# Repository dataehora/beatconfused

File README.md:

# BeatConfused

A small web studio of fast, elegant, install-free music tools. Every tool
is plain HTML, CSS and vanilla JavaScript with the Web Audio API — no build
step, no dependencies, no accounts, works offline after first load.

Live at [beatconfused.com](https://beatconfused.com).

## Tools

| Tool | Path | What it does |
| --- | --- | --- |
| **Metronome** | [`/metronome/`](https://beatconfused.com/metronome/) | Tap tempo, organized time signatures, beat subdivisions, counting modes, sound styles, and pulse / number / pendulum visuals. |
| **Tuner** | [`/tuner/`](https://beatconfused.com/tuner/) | Chromatic instrument tuner with needle, strobe and LED-meter displays, an adjustable A4 reference pitch, historical tuning standards, a test-tone generator, and a spectrum analyser. |
| **Octave Strobe Tuner** | [`/strobetuner/`](https://beatconfused.com/strobetuner/) | Identifies the note being played and shows its tuning across every octave at once on a single strobe disc. |
| **Chromatic Strobe Tuner** | [`/multistrobe/`](https://beatconfused.com/multistrobe/) | One dedicated strobe wheel per note, laid out like a piano keyboard, each with a ring per octave across the 88-key range. |
| **Luthier Tuning** | [`/luthier/`](https://beatconfused.com/luthier/) | Live spectrogram for luthiers and tuners: a slowly decaying live spectrum over a peak-hold record of every frequency, a sustain waterfall, harmonic guides, and a full-range / audible-only toggle. |

## Repository layout

```
index.html            Studio landing page (tool cards + JSON-LD)
styles.css             Landing-page styles
metronome/             Metronome — index.html, script.js, styles.css, Assets/
tuner/                 Tuner — index.html, script.js, styles.css
strobetuner/           Octave Strobe Tuner — index.html, script.js, styles.css
multistrobe/           Chromatic Strobe Tuner — index.html, script.js, styles.css
luthier/               Luthier Tuning (spectrogram) — index.html, script.js, styles.css
etutti/                eTutti (work in progress, unlisted) — Web MIDI page, Teensy firmware/,
                       hardware/ (eTuttino board v0.7 + case SPEC v9), manuais/, models/
binfacevsfarage/       Standalone browser game (not linked from the studio)
shared/                Assets shared across tools
CNAME, robots.txt, sitemap.xml   Hosting + crawl metadata
```

## Metronome controls

### Tempo
- **Slider** / **input field** — smooth or direct BPM entry (40–240)
- **+/- buttons** — step by 5 BPM
- **Tap tempo** — tap the button or press `T` to detect BPM
- **Arrow keys** — Up / Down to adjust BPM

### Beat settings
- **Time signature** — organized simple, compound and odd meters
- **Beat subdivision** — split each beat into more pulses
- **Tempo counting** — beat count, measure + beat, or hidden
- **Beat visual** — pulse, numbers, or pendulum
- **Sound style** — electronic, bossa, jazz, wood, cymbal, cowbell
- **Sound / vibration toggles** and **volume control**

### Keyboard shortcuts
- **Space** — start / stop
- **Arrow Up / Down** — BPM ±5
- **T** — tap tempo

### Custom sounds
Drop `{style}_{accent|beat|subdivision}` audio files (`.mp3`, then `.ogg`,
then `.wav`) into `metronome/Assets/` and they replace the synthesised click
for that combination. Anything not supplied keeps the built-in sound, so the
metronome always has audio even with no custom assets.

## Tuner controls

- **Start Tuner** — vintage-style slide switch above the display; turns the
  microphone on. A "no signal" sign appears below the display after ~3s of
  silence while running.
- **Display** — needle, strobe or LED meter
- **Input Monitor and Test Tone** — collapsed by default; microphone gain
  boost and a live level meter, plus a pure tone (with its own frequency,
  fine-tuning and volume controls) fed straight into the tuner and the
  speakers, no mic needed — the same panel /strobetuner/ and /multistrobe/
  use too
- **Spectrum Analyser** — vintage or modern style
- **Tuning Standard and Reference Pitch** — Equal Temperament plus
  Vallotti, Young II, 1/4-comma meantone and Just Intonation (each built
  from first principles), and an A4 reference from 392–466 Hz with
  historical presets (French Baroque, Baroque, Verdi, Standard, Modern,
  Italian Renaissance)
- **Frequency Table** — every note of an 88-key piano (octaves down the
  rows, notes across the columns) under the selected Tuning Standard and
  Reference Pitch, with a live cents deviation next to whichever note is
  sounding

## Luthier Tuning controls

- **Start Listening** — the same slide switch as the tuners (or `Space`)
- **Full range / Audible only** — everything the microphone captures (up
  to half its sample rate, with infrasound and ultrasound shaded) or just
  20 Hz – 20 kHz
- **Live curve** — the current spectrum; each frequency falls back at the
  **Decay speed** (dB/s) so a note's ring-out stays visible
- **Peak hold** — the pale-blue background graph: the loudest level each
  frequency has reached since the last **Reset peak hold**. **On** keeps
  it until reset; **Temporary** holds each maximum for 2 s, then lets it
  fall at the same Decay speed as the live curve; **Off** hides it
- **Sustain history** — a 12-second waterfall under the display
- **Cursor** — hover / tap for frequency, nearest note, live and peak dB,
  plus dashed guides at 2×, 3×, 4×… to judge inharmonicity
- **Input gain** — boosts quiet instruments

## Technical stack

- **HTML5 / CSS3** — semantic structure, gradients and animations
- **Web Audio API** — high-precision timing, autocorrelation pitch
  detection, Goertzel per-octave analysis for the strobe tools
- **Vanilla JavaScript** — no dependencies, no build step
- **Structured data + crawl files** — JSON-LD, `robots.txt`, `sitemap.xml`

## Development

Everything is static — serve the repo root with any static file server:

```bash
git clone https://github.com/dataehora/beatconfused.git
cd beatconfused
python3 -m http.server 8000
# then open http://localhost:8000/
```

## Deployment

Served via GitHub Pages on the `beatconfused.com` domain (`CNAME`). Any
static host with HTTPS works — no server-side code.

## License

MIT License — feel free to use and modify.

## Contributing

Contributions are welcome. Please open a Pull Request.

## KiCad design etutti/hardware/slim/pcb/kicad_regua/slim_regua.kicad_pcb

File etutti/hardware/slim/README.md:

# eTutti Slim

Versão de 32 teclas, a mais fina possível, independente do Student V4.

- `SPEC.md` — especificação vigente (R1SL). Comece por aqui.
- `conceito/` — material do conceito feito no Chat: renders, cortes, plantas, desenho dos knobs e scripts que geraram tudo.
- `fornecimento/gateron/` — desenho oficial e STEP do switch KS‑33D.
- Pastas que o Code vai criar: `pcb/` (KiCad), `case/`, `firmware/` e os relatórios `ELETRONICA.md`, `FIRMWARE.md`, `POSICIONAMENTO.md`, `ROTEAMENTO.md` e `FIT_CHECK.md`.

Etapas: 1) componentes e lógica → portão A · 2) posicionamento (régua e placa principal em sessões separadas) → portão B · 3) roteamento (idem) → portão C.

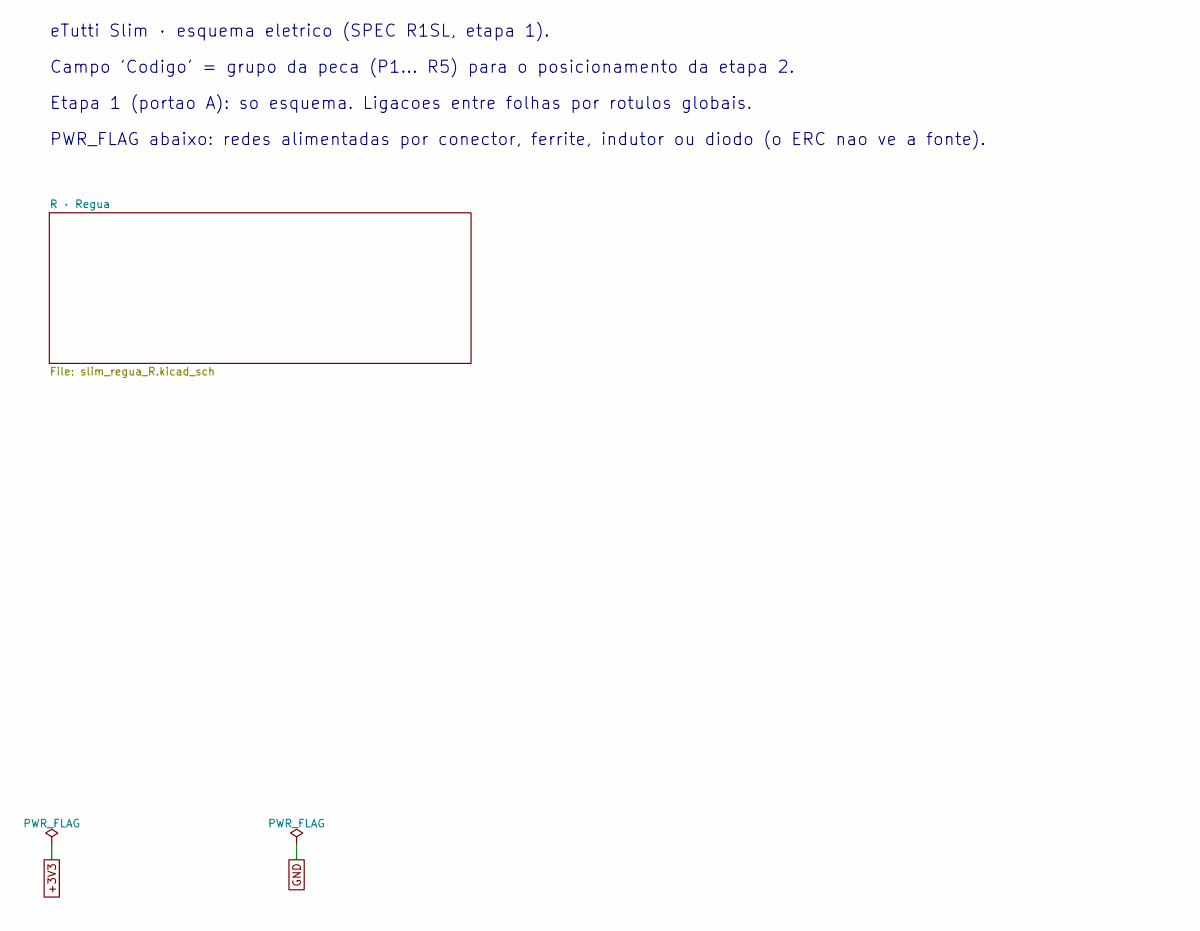
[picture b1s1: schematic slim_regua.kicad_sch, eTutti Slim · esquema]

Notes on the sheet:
eTutti Slim · esquema eletrico (SPEC R1SL, etapa 1).
Campo 'Codigo' = grupo da peca (P1... R5) para o posicionamento da etapa 2.
Etapa 1 (portao A): so esquema. Ligacoes entre folhas por rotulos globais.
PWR_FLAG abaixo: redes alimentadas por conector, ferrite, indutor ou diodo (o ERC nao ve a fonte).

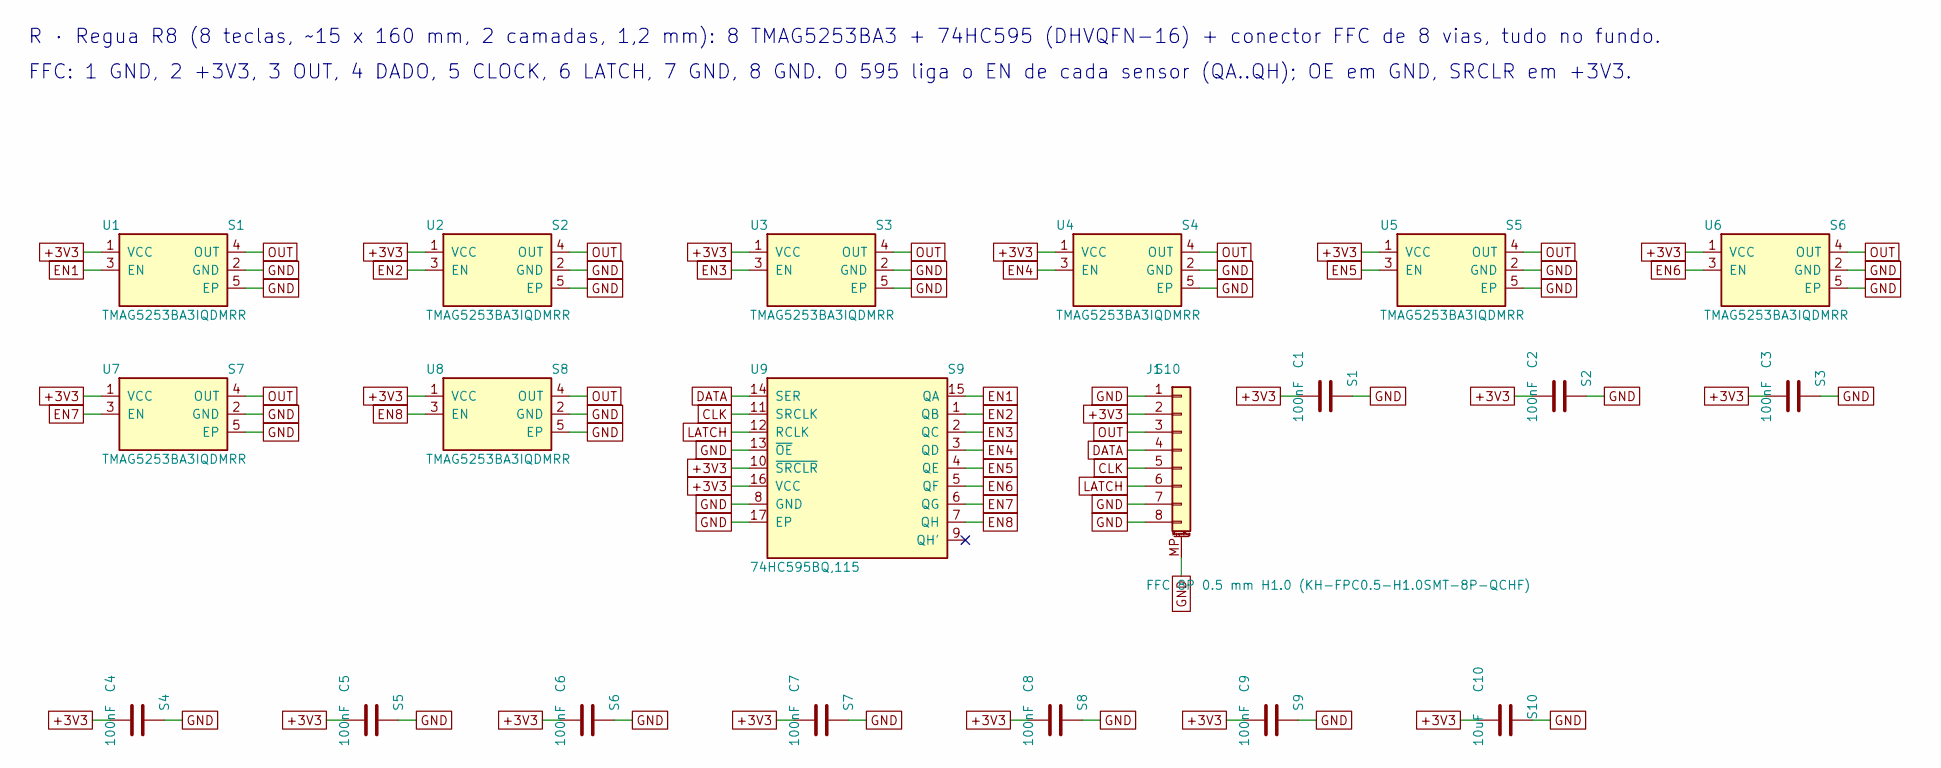
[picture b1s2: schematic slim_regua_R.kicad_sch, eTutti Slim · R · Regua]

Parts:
C1, C2, C3, C4, C5, C6, C7, C8, C9: 100nF; C_0402_1005Metric; LCSC C1525
C10: 10uF; C_0805_2012Metric; LCSC C15850
J1: FFC 8P 0.5 mm H1.0 (KH-FPC0.5-H1.0SMT-8P-QCHF); FFC_8P_0.5_KH-H1.0; LCSC C3250113
U1, U2, U3, U4, U5, U6, U7, U8: TMAG5253BA3IQDMRR; TMAG5253_X2SON4_EE; LCSC C22401868
U9: 74HC595BQ,115; HC595_DHVQFN16_EE; LCSC C730243

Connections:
+3V3: C1.1, C2.1, C3.1, C4.1, C5.1, C6.1, C7.1, C8.1, C9.1, C10.1, J1.2, U1.1 (VCC), U2.1 (VCC), U3.1 (VCC), U4.1 (VCC), U5.1 (VCC), U6.1 (VCC), U7.1 (VCC), U8.1 (VCC), U9.10 (~SRCLR), U9.16 (VCC)
CLK: J1.5, U9.11 (SRCLK)
DATA: J1.4, U9.14 (SER)
EN1: U1.3 (EN), U9.15 (QA)
EN2: U2.3 (EN), U9.1 (QB)
EN3: U3.3 (EN), U9.2 (QC)
EN4: U4.3 (EN), U9.3 (QD)
EN5: U5.3 (EN), U9.4 (QE)
EN6: U6.3 (EN), U9.5 (QF)
EN7: U7.3 (EN), U9.6 (QG)
EN8: U8.3 (EN), U9.7 (QH)
GND: C1.2, C2.2, C3.2, C4.2, C5.2, C6.2, C7.2, C8.2, C9.2, C10.2, J1.1, J1.7, J1.8, J1.MP (MountPin), U1.2 (GND), U1.5 (EP), U2.2 (GND), U2.5 (EP), U3.2 (GND), U3.5 (EP), U4.2 (GND), U4.5 (EP), U5.2 (GND), U5.5 (EP), U6.2 (GND), U6.5 (EP), U7.2 (GND), U7.5 (EP), U8.2 (GND), U8.5 (EP), U9.8 (GND), U9.13 (~OE), U9.17 (EP)
LATCH: J1.6, U9.12 (RCLK)
OUT: J1.3, U1.4 (OUT), U2.4 (OUT), U3.4 (OUT), U4.4 (OUT), U5.4 (OUT), U6.4 (OUT), U7.4 (OUT), U8.4 (OUT)

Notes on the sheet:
R · Regua R8 (8 teclas, ~15 x 160 mm, 2 camadas, 1,2 mm): 8 TMAG5253BA3 + 74HC595 (DHVQFN-16) + conector FFC de 8 vias, tudo no fundo.
FFC: 1 GND, 2 +3V3, 3 OUT, 4 DADO, 5 CLOCK, 6 LATCH, 7 GND, 8 GND. O 595 liga o EN de cada sensor (QA..QH); OE em GND, SRCLR em +3V3.

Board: 2 copper layers, 30 parts (20 on the bottom side), 14 nets, no tracks yet.

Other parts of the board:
H1, H2: MountingHole_2.2mm_M2
SW1, SW2, SW3, SW4, SW5, SW6, SW7, SW8: KS-33D (furos); KS33D_holes

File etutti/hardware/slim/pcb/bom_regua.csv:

lcsc,valor,classe_jlc,qtd,referencias,preco_unit_usd_est
C1525,100nF,Basic,9,C1 C2 C3 C4 C5 C6 C7 C8 C9,0.001
C15850,10uF,Basic,1,C10,0.008
C3250113,FFC 8P 0.5 mm H1.0 (KH-FPC0.5-H1.0SMT-8P-QCHF),Extended,1,J1,0.100
C22401868,TMAG5253BA3IQDMRR,Extended,8,U1 U2 U3 U4 U5 U6 U7 U8,0.600
C730243,"74HC595BQ,115",Extended,1,U9,0.176

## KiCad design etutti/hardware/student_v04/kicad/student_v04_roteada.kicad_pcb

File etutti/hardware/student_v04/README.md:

# eTutti Student V4 — base de trabalho

SPEC: `SPEC.md` (R1V4 + R2V4, do Chat; o Code nunca a edita). Relatórios do Code (português, citam "R2V4"):
`FIT_CHECK.md` (design), `ELETRONICA.md` (eletrônica), `FIRMWARE.md` (programação e som).

Esta pasta nasceu da `student_v03/` (R1V4, tarefa 1): só **scripts e fontes** (esquema, geometria, pcb, case, estudos,
fornecimento), sem `fab/`, renders, STEP/STL nem saídas geradas. A V3, a V2 e a V1 **não são alteradas**.
Fase B (R3V4): `pcb/schematic.py` (esquema V4, ERC), `pcb/posiciona_v4.py` (placa principal sem trilhas), `pcb/vistas_v4.py` (imagens), `bom_v4.py`; arquivos KiCad `kicad/student_v04.*`. Os demais scripts herdados da V3 (`build_sem_rota.py`, `pcb/build_board_v3.py`, `refaz_usb.py`...) não valem para a V4.
Páginas, Blender e passos de manual da V3 não foram copiados (página e manual ficam para depois, decisão 19).

## Ordem de execução (herdada da V3; ajustar à medida que a V4 diverge)

1. `python geometria.py` (stdlib).
2. `python pcb/schematic.py` (esquema + ERC + netlist), `pcb/export_furos.py` e `pcb/export_fp.py` (KiCad python).
3. Placa: `build_sem_rota.py` -> `pcb/build_board_v3.py` -> `pcb/troca_jack.py` -> `pcb/refaz_usb.py` -> `pcb/costura_usb.py` (KiCad python).
   Na V4 o posicionamento (Fase B) e o roteamento (Fase C, agente `roteamento`) são etapas separadas.
4. `fab.py`, `bom_v3.py`, `auditoria_pinos.py`.
5. Case (venv CadQuery): `case/case.py`, `case/fit_check.py`, `case/fit_extra.py`, `case/render.py`, `estudos/acustica.py`;
   `estudos/flexao.py` (KiCad python).

KiCad python: `C:/Program Files/KiCad/10.0/bin/python.exe`. CadQuery: `C:/Users/julia/.venvs/cadquery/Scripts/python.exe`.

## Réguas (R11V4)
Dois desenhos (R8 de 8 posições, R4 de 4), quatro variantes por BOM (R8, R8E, R4, R4E: "E" = com o OUT). Ordem, com `REGUA_N=8` ou `4`:
`python pcb/regua/schematic_regua.py` -> KiCad python `pcb/regua/posiciona_regua.py` -> KiCad python `pcb/regua/pacotes_regua.py` (BOM e CPL em `fab/regua/`) ->
KiCad python `MODO=regua PAINEL_N=2|4|5 pcb/regua/fab_regua.py` (painéis) -> venv CadQuery `pcb/regua/vistas_regua.py`; custo: `pcb/regua/custo_r11.py`.
Entrega ao roteamento: `pcb/regua/ROTEAMENTO_ENTREGA.md`; folha de cotação: `fab/regua/LEIAME_COTACAO.md`. Nunca rodar `posiciona_regua.py` sobre uma placa roteada (use `REGUA_BOARD`).

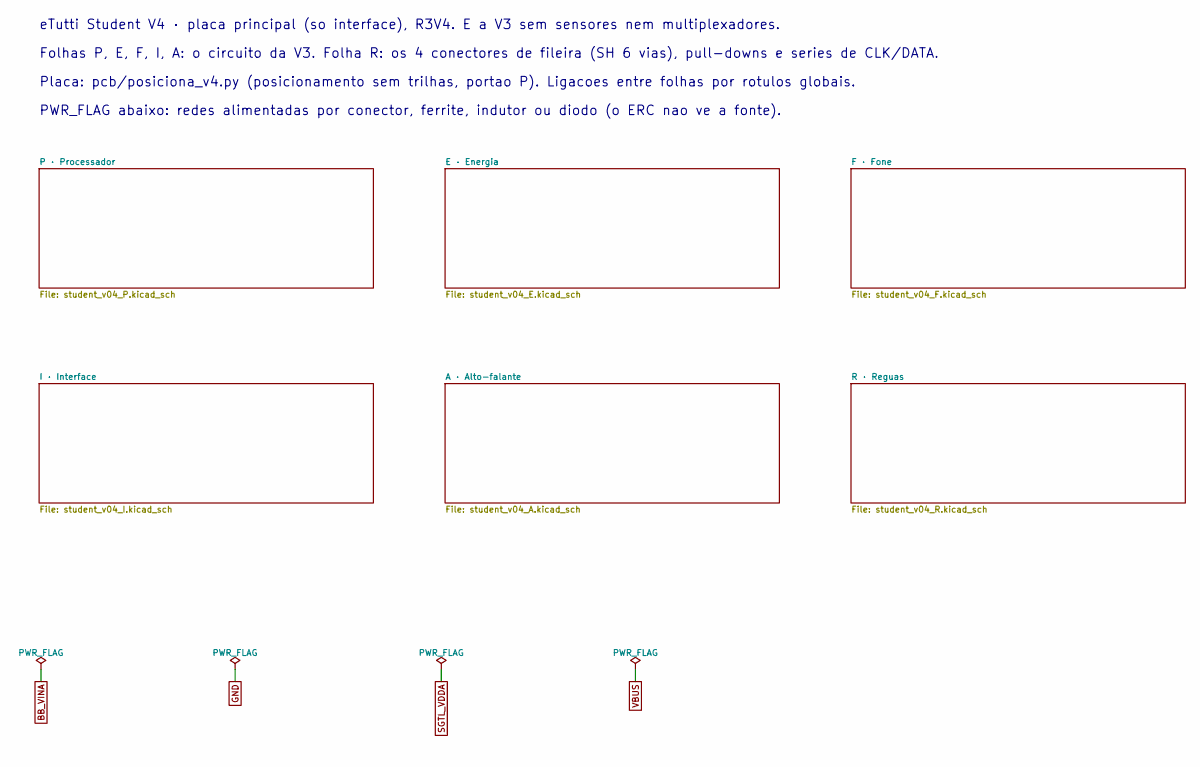
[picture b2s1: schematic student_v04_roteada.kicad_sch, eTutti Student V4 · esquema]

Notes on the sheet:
eTutti Student V4 · placa principal (so interface), R3V4. E a V3 sem sensores nem multiplexadores.
Folhas P, E, F, I, A: o circuito da V3. Folha R: os 4 conectores de fileira (SH 6 vias), pull-downs e series de CLK/DATA.
Placa: pcb/posiciona_v4.py (posicionamento sem trilhas, portao P). Ligacoes entre folhas por rotulos globais.
PWR_FLAG abaixo: redes alimentadas por conector, ferrite, indutor ou diodo (o ERC nao ve a fonte).

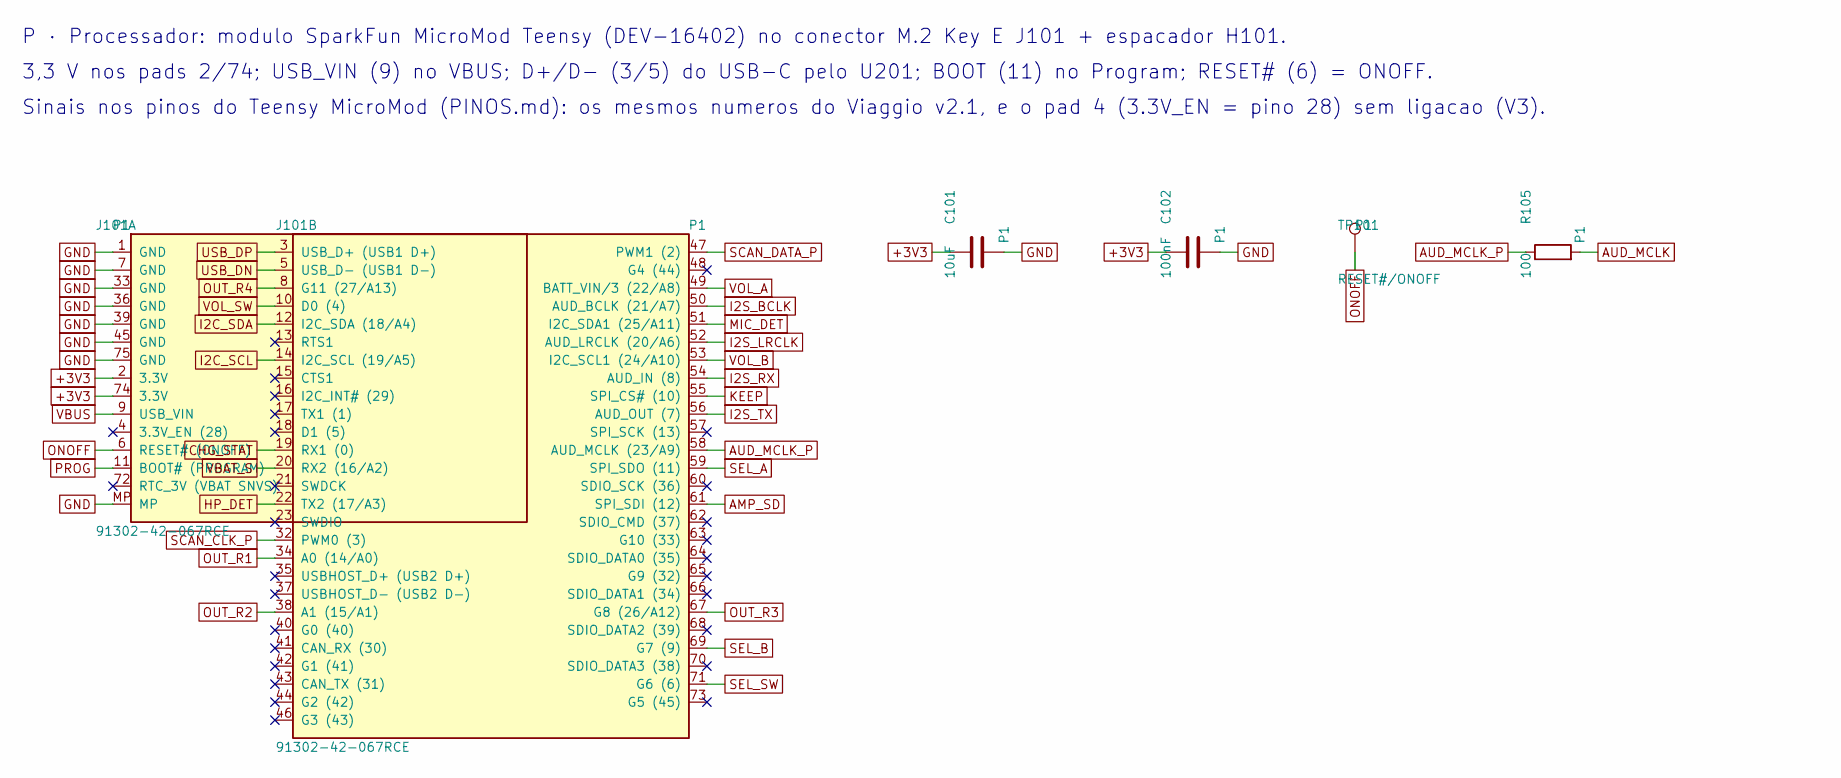
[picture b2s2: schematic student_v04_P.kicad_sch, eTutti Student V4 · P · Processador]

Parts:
C101: 10uF; C_0805_2012Metric; LCSC C15850
C102: 100nF; C_0402_1005Metric; LCSC C1525
J101: 91302-42-067RCE; M.2_E_H4.2_UMAX_91302-42-067; LCSC C48985906
R105: 100; R_0402_1005Metric; LCSC C25076
TP101: RESET#/ONOFF; TestPoint_Pad_D1.5mm

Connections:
+3V3: C101.1, C102.1, J101.2 (3.3V), J101.74 (3.3V); also elsewhere on the board
AMP_SD: J101.61 (SPI_SDI (12)); also elsewhere on the board
AUD_MCLK: R105.2; also elsewhere on the board
AUD_MCLK_P: J101.58 (AUD_MCLK (23/A9)), R105.1
CHG_STAT: J101.19 (RX1 (0)); also elsewhere on the board
GND: C101.2, C102.2, J101.1 (GND), J101.7 (GND), J101.33 (GND), J101.36 (GND), J101.39 (GND), J101.45 (GND), J101.75 (GND), J101.MP; also elsewhere on the board
HP_DET: J101.22 (TX2 (17/A3)); also elsewhere on the board
I2C_SCL: J101.14 (I2C_SCL (19/A5)); also elsewhere on the board
I2C_SDA: J101.12 (I2C_SDA (18/A4)); also elsewhere on the board
I2S_BCLK: J101.50 (AUD_BCLK (21/A7)); also elsewhere on the board
I2S_LRCLK: J101.52 (AUD_LRCLK (20/A6)); also elsewhere on the board
I2S_RX: J101.54 (AUD_IN (8)); also elsewhere on the board
I2S_TX: J101.56 (AUD_OUT (7)); also elsewhere on the board
KEEP: J101.55 (SPI_CS# (10)); also elsewhere on the board
MIC_DET: J101.51 (I2C_SDA1 (25/A11)); also elsewhere on the board
ONOFF: J101.6 (RESET# (ONOFF)), TP101.1; also elsewhere on the board
OUT_R1: J101.34 (A0 (14/A0)); also elsewhere on the board
OUT_R2: J101.38 (A1 (15/A1)); also elsewhere on the board
OUT_R3: J101.67 (G8 (26/A12)); also elsewhere on the board
OUT_R4: J101.8 (G11 (27/A13)); also elsewhere on the board
PROG: J101.11 (BOOT# (PROGRAM)); also elsewhere on the board
SCAN_CLK_P: J101.32 (PWM0 (3)); also elsewhere on the board
SCAN_DATA_P: J101.47 (PWM1 (2)); also elsewhere on the board
SEL_A: J101.59 (SPI_SDO (11)); also elsewhere on the board
SEL_B: J101.69 (G7 (9)); also elsewhere on the board
SEL_SW: J101.71 (G6 (6)); also elsewhere on the board
USB_DN: J101.5 (USB_D- (USB1 D-)); also elsewhere on the board
USB_DP: J101.3 (USB_D+ (USB1 D+)); also elsewhere on the board
VBAT_S: J101.20 (RX2 (16/A2)); also elsewhere on the board
VBUS: J101.9 (USB_VIN); also elsewhere on the board
VOL_A: J101.49 (BATT_VIN/3 (22/A8)); also elsewhere on the board
VOL_B: J101.53 (I2C_SCL1 (24/A10)); also elsewhere on the board
VOL_SW: J101.10 (D0 (4)); also elsewhere on the board

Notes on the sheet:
P · Processador: modulo SparkFun MicroMod Teensy (DEV-16402) no conector M.2 Key E J101 + espacador H101.
3,3 V nos pads 2/74; USB_VIN (9) no VBUS; D+/D- (3/5) do USB-C pelo U201; BOOT (11) no Program; RESET# (6) = ONOFF.
Sinais nos pinos do Teensy MicroMod (PINOS.md): os mesmos numeros do Viaggio v2.1, e o pad 4 (3.3V_EN = pino 28) sem ligacao (V3).

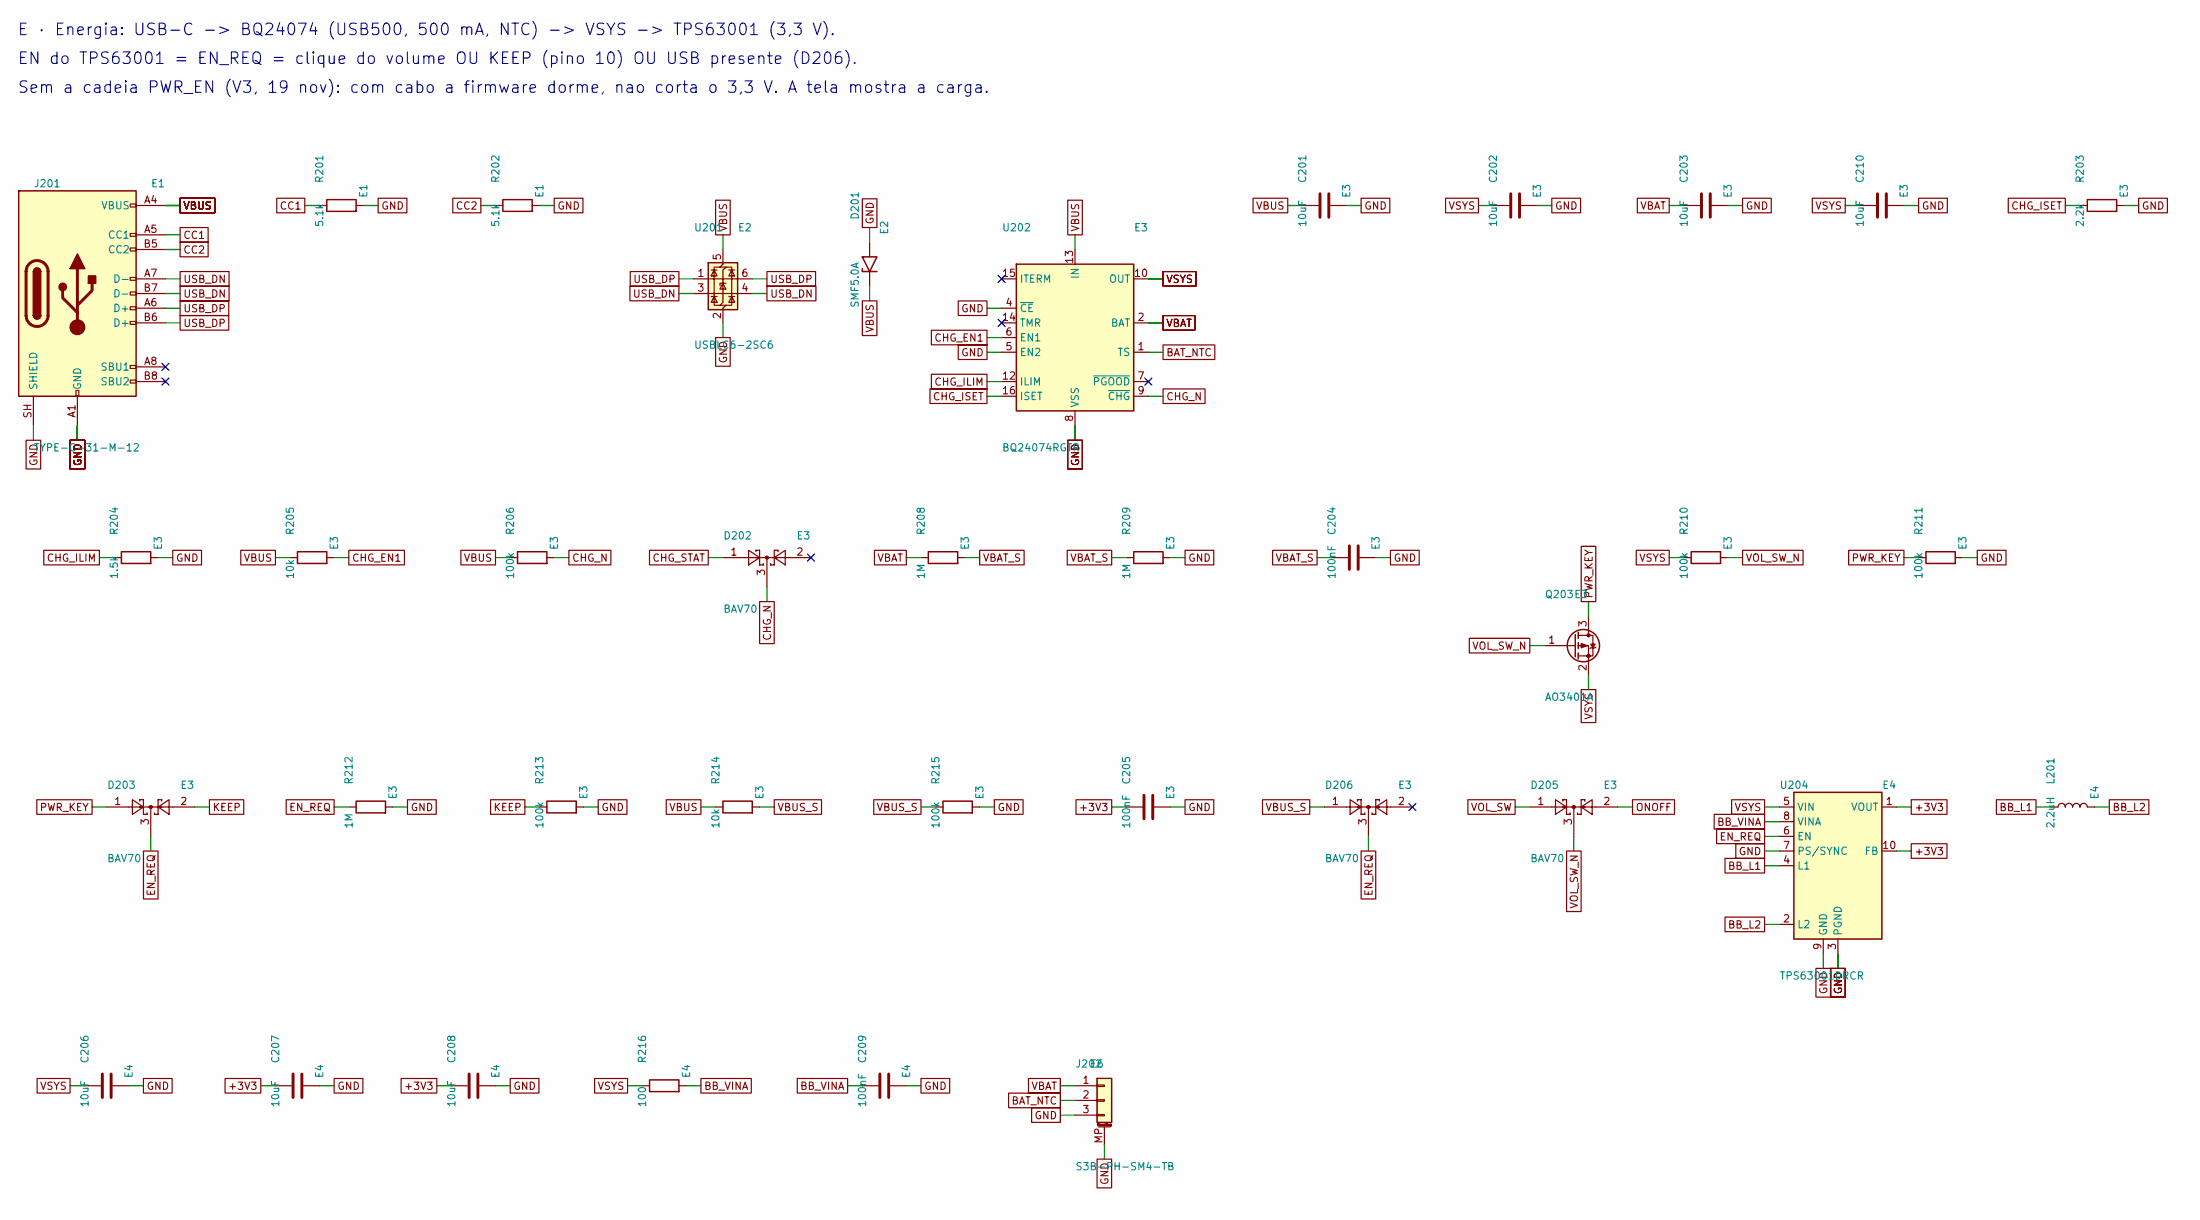
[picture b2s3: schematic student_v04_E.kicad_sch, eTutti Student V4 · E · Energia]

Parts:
C201, C202, C203, C206, C207, C208: 10uF; C_0805_2012Metric; LCSC C15850
C204, C205, C209: 100nF; C_0402_1005Metric; LCSC C1525
C210: 10uF; C_0603_1608Metric; LCSC C19702
D201: SMF5.0A; D_SOD-123F; LCSC C151296
D202, D203, D205, D206: BAV70; SOT-23; LCSC C68978
J201: TYPE-C-31-M-12; USB_C_Receptacle_HRO_TYPE-C-31-M-12; LCSC C165948
J202: S3B-PH-SM4-TB; JST_PH_S3B-PH-SM4-TB_1x03-1MP_P2.00mm_Horizontal; LCSC C265101
L201: 2.2uH; L_Changjiang_FNR4020S; LCSC C167825
Q203: AO3401A; SOT-23; LCSC C15127
R201, R202: 5.1k; R_0402_1005Metric; LCSC C25905
R203: 2.2k; R_0402_1005Metric; LCSC C25879
R204: 1.5k; R_0402_1005Metric; LCSC C25867
R205, R214: 10k; R_0402_1005Metric; LCSC C25744
R206, R210, R211, R213, R215: 100k; R_0402_1005Metric; LCSC C25741
R208, R209, R212: 1M; R_0402_1005Metric; LCSC C26083
R216: 100; R_0402_1005Metric; LCSC C25076
U201: USBLC6-2SC6; SOT-23-6; LCSC C7519
U202: BQ24074RGTR; VQFN-16-1EP_3x3mm_P0.5mm_EP1.6x1.6mm; LCSC C54313
U204: TPS63001DRCR; Texas_DRC0010J; LCSC C28060

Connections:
+3V3: C205.1, C207.1, C208.1, U204.1 (VOUT), U204.10 (FB); also elsewhere on the board
BAT_NTC: J202.2, U202.1 (TS)
BB_L1: L201.1, U204.4 (L1)
BB_L2: L201.2, U204.2 (L2)
BB_VINA: C209.1, R216.2, U204.8 (VINA)
CC1: J201.A5 (CC1), R201.1
CC2: J201.B5 (CC2), R202.1
CHG_EN1: R205.2, U202.6 (EN1)
CHG_ILIM: R204.1, U202.12 (ILIM)
CHG_ISET: R203.1, U202.16 (ISET)
CHG_N: D202.3, R206.2, U202.9 (~CHG)
CHG_STAT: D202.1; also elsewhere on the board
EN_REQ: D203.3, D206.3, R212.1, U204.6 (EN)
GND: C201.2, C202.2, C203.2, C204.2, C205.2, C206.2, C207.2, C208.2, C209.2, C210.2, D201.2 (A2), J201.A1 (GND), J201.A12 (GND), J201.B1 (GND), J201.B12 (GND), J201.SH (SHIELD), J202.3, J202.MP (MountPin), R201.2, R202.2, R203.2, R204.2, R209.2, R211.2, R212.2, R213.2, R215.2, U201.2 (GND), U202.4 (~CE), U202.5 (EN2), U202.8 (VSS), U202.17 (VSS), U204.3 (PGND), U204.7 (PS/SYNC), U204.9 (GND), U204.11 (PGND); also elsewhere on the board
KEEP: D203.2, R213.1; also elsewhere on the board
ONOFF: D205.2; also elsewhere on the board
PWR_KEY: D203.1, Q203.3 (D), R211.1
USB_DN: J201.A7 (D-), J201.B7 (D-), U201.3 (I/O2), U201.4 (I/O2); also elsewhere on the board
USB_DP: J201.A6 (D+), J201.B6 (D+), U201.1 (I/O1), U201.6 (I/O1); also elsewhere on the board
VBAT: C203.1, J202.1, R208.1, U202.2 (BAT), U202.3 (BAT)
VBAT_S: C204.1, R208.2, R209.1; also elsewhere on the board
VBUS: C201.1, D201.1 (A1), J201.A4 (VBUS), J201.A9 (VBUS), J201.B4 (VBUS), J201.B9 (VBUS), R205.1, R206.1, R214.1, U201.5 (VBUS), U202.13 (IN); also elsewhere on the board
VBUS_S: D206.1, R214.2, R215.1
VOL_SW: D205.1; also elsewhere on the board
VOL_SW_N: D205.3, Q203.1 (G), R210.2; also elsewhere on the board
VSYS: C202.1, C206.1, C210.1, Q203.2 (S), R210.1, R216.1, U202.10 (OUT), U202.11 (OUT), U204.5 (VIN); also elsewhere on the board

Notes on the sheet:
E · Energia: USB-C -> BQ24074 (USB500, 500 mA, NTC) -> VSYS -> TPS63001 (3,3 V).
EN do TPS63001 = EN_REQ = clique do volume OU KEEP (pino 10) OU USB presente (D206).
Sem a cadeia PWR_EN (V3, 19 nov): com cabo a firmware dorme, nao corta o 3,3 V. A tela mostra a carga.

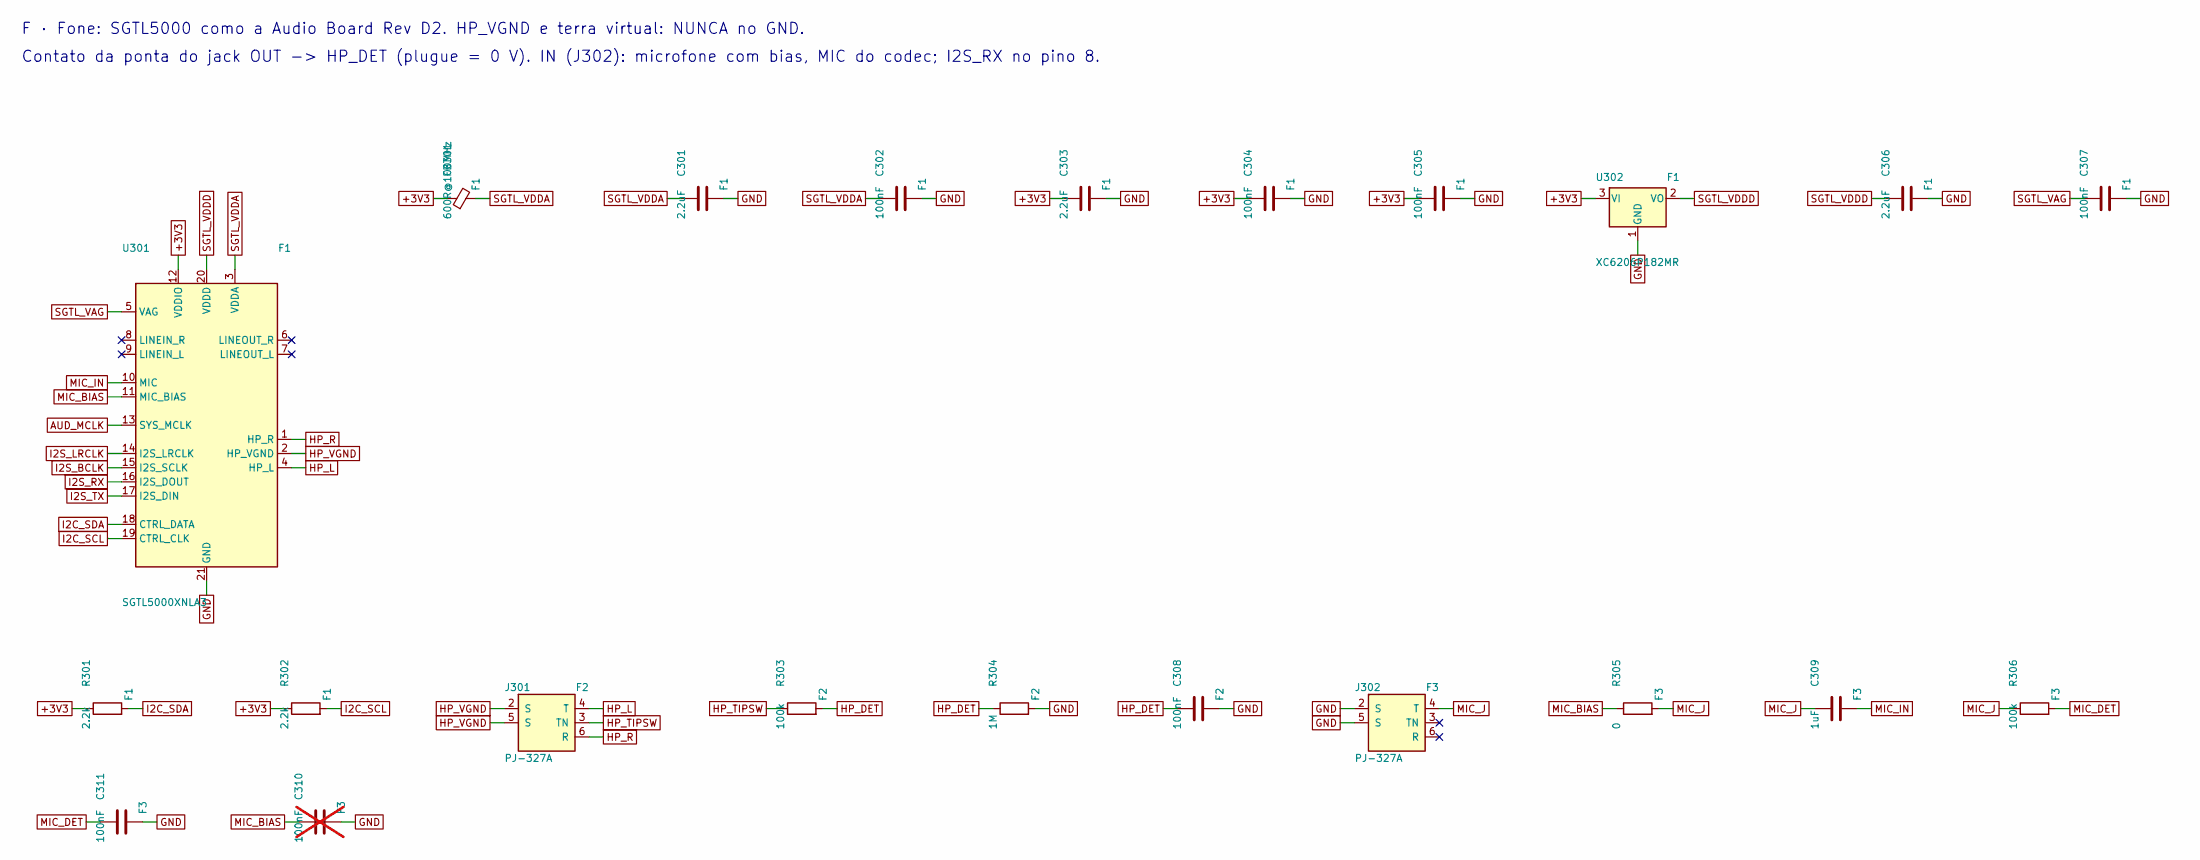
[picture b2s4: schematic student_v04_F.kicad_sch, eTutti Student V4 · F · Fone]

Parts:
C301, C303, C306: 2.2uF; C_0402_1005Metric; LCSC C12530
C302, C304, C305, C307, C308, C311: 100nF; C_0402_1005Metric; LCSC C1525
C309: 1uF; C_0402_1005Metric; LCSC C52923
C310: 100nF; C_0402_1005Metric; LCSC C1525; not fitted
FB301: 600R@100MHz; L_0603_1608Metric; LCSC C1002
J301, J302: PJ-327A; Jack_3.5mm_PJ-327A_SMD; LCSC C49284723
R301, R302: 2.2k; R_0402_1005Metric; LCSC C25879
R303, R306: 100k; R_0402_1005Metric; LCSC C25741
R304: 1M; R_0402_1005Metric; LCSC C26083
R305: 0; R_0402_1005Metric; LCSC C17168
U301: SGTL5000XNLA3; QFN-20-1EP_3x3mm_P0.4mm_EP1.65x1.65mm; LCSC C2651833
U302: XC6206P182MR; SOT-23-3; LCSC C347373

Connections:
+3V3: C303.1, C304.1, C305.1, FB301.1, R301.1, R302.1, U301.12 (VDDIO), U302.3 (VI); also elsewhere on the board
AUD_MCLK: U301.13 (SYS_MCLK); also elsewhere on the board
GND: C301.2, C302.2, C303.2, C304.2, C305.2, C306.2, C307.2, C308.2, C310.2, C311.2, J302.2 (S), J302.5 (S), R304.2, U301.21 (GND), U302.1 (GND); also elsewhere on the board
HP_DET: C308.1, R303.2, R304.1; also elsewhere on the board
HP_L: J301.4 (T), U301.4 (HP_L)
HP_R: J301.6 (R), U301.1 (HP_R)
HP_TIPSW: J301.3 (TN), R303.1
HP_VGND: J301.2 (S), J301.5 (S), U301.2 (HP_VGND)
I2C_SCL: R302.2, U301.19 (CTRL_CLK); also elsewhere on the board
I2C_SDA: R301.2, U301.18 (CTRL_DATA); also elsewhere on the board
I2S_BCLK: U301.15 (I2S_SCLK); also elsewhere on the board
I2S_LRCLK: U301.14 (I2S_LRCLK); also elsewhere on the board
I2S_RX: U301.16 (I2S_DOUT); also elsewhere on the board
I2S_TX: U301.17 (I2S_DIN); also elsewhere on the board
MIC_BIAS: C310.1, R305.1, U301.11 (MIC_BIAS)
MIC_DET: C311.1, R306.2; also elsewhere on the board
MIC_IN: C309.2, U301.10 (MIC)
MIC_J: C309.1, J302.4 (T), R305.2, R306.1
SGTL_VAG: C307.1, U301.5 (VAG)
SGTL_VDDA: C301.1, C302.1, FB301.2, U301.3 (VDDA)
SGTL_VDDD: C306.1, U301.20 (VDDD), U302.2 (VO)

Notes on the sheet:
F · Fone: SGTL5000 como a Audio Board Rev D2. HP_VGND e terra virtual: NUNCA no GND.
Contato da ponta do jack OUT -> HP_DET (plugue = 0 V). IN (J302): microfone com bias, MIC do codec; I2S_RX no pino 8.

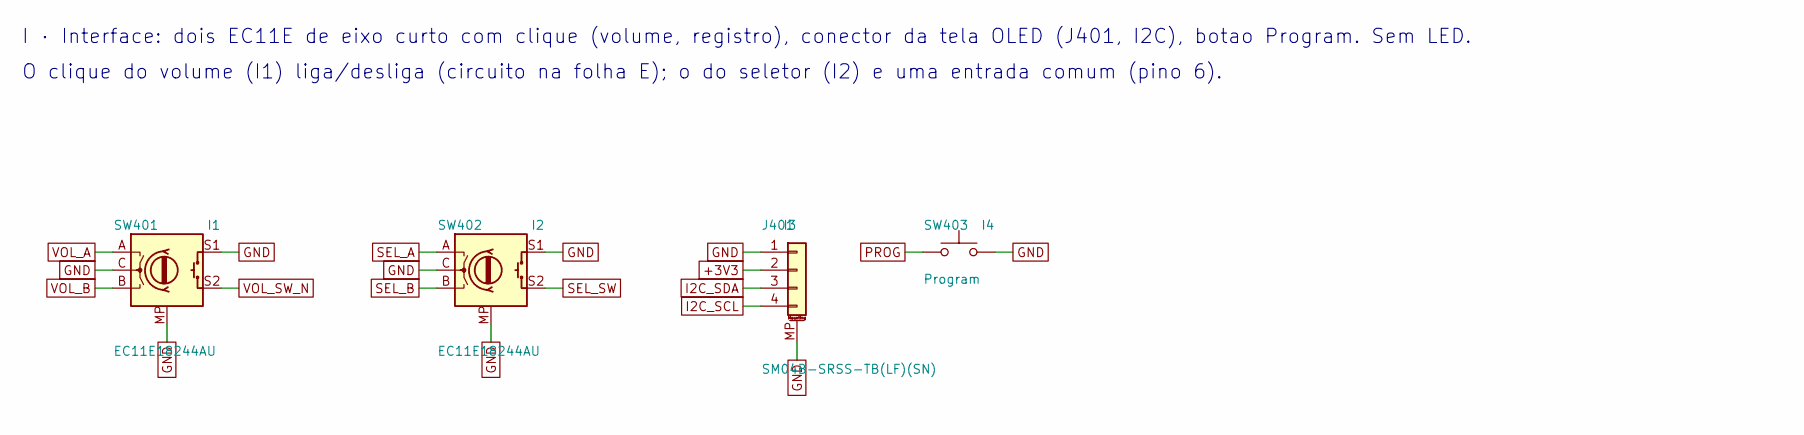
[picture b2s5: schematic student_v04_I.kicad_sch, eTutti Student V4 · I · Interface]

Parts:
J401: SM04B-SRSS-TB(LF)(SN); JST_SH_SM04B-SRSS-TB_1x04-1MP_P1.00mm_Horizontal; LCSC C160404
SW401, SW402: EC11E18244AU; RotaryEncoder_Alps_EC11E-Switch_Vertical_H20mm; LCSC C202365
SW403: Program; SW_Push_1P1T_XKB_TS-1187A; LCSC C318884

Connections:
+3V3: J401.2; also elsewhere on the board
GND: J401.1, J401.MP (MountPin), SW401.C, SW401.MP, SW401.S1, SW402.C, SW402.MP, SW402.S1, SW403.2; also elsewhere on the board
I2C_SCL: J401.4; also elsewhere on the board
I2C_SDA: J401.3; also elsewhere on the board
PROG: SW403.1; also elsewhere on the board
SEL_A: SW402.A; also elsewhere on the board
SEL_B: SW402.B; also elsewhere on the board
SEL_SW: SW402.S2; also elsewhere on the board
VOL_A: SW401.A; also elsewhere on the board
VOL_B: SW401.B; also elsewhere on the board
VOL_SW_N: SW401.S2; also elsewhere on the board

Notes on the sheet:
I · Interface: dois EC11E de eixo curto com clique (volume, registro), conector da tela OLED (J401, I2C), botao Program. Sem LED.
O clique do volume (I1) liga/desliga (circuito na folha E); o do seletor (I2) e uma entrada comum (pino 6).

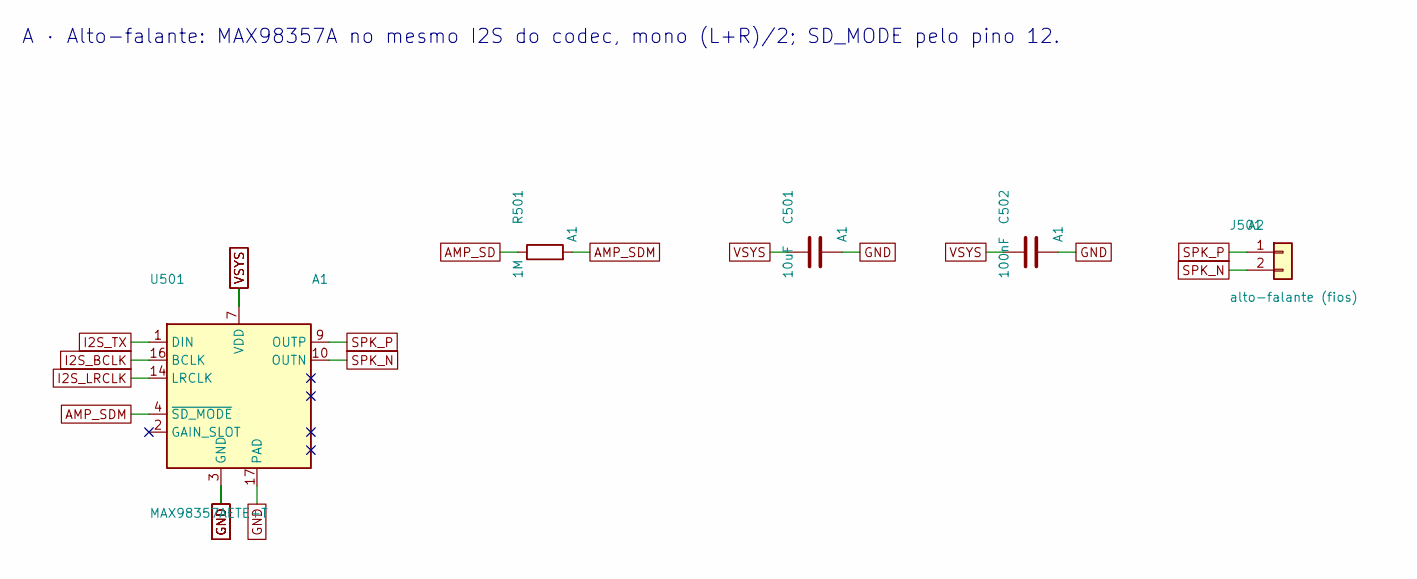
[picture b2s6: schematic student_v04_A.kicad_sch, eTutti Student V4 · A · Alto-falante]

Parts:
C501: 10uF; C_0805_2012Metric; LCSC C15850
C502: 100nF; C_0402_1005Metric; LCSC C1525
J501: alto-falante (fios); SolderWire-0.127sqmm_1x02_P3.7mm_D0.48mm_OD1mm
R501: 1M; R_0402_1005Metric; LCSC C26083
U501: MAX98357AETE+T; TQFN-16-1EP_3x3mm_P0.5mm_EP1.23x1.23mm; LCSC C910544

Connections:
AMP_SD: R501.1; also elsewhere on the board
AMP_SDM: R501.2, U501.4 (~SD_MODE)
GND: C501.2, C502.2, U501.3 (GND), U501.11 (GND), U501.15 (GND), U501.17 (PAD); also elsewhere on the board
I2S_BCLK: U501.16 (BCLK); also elsewhere on the board
I2S_LRCLK: U501.14 (LRCLK); also elsewhere on the board
I2S_TX: U501.1 (DIN); also elsewhere on the board
SPK_N: J501.2, U501.10 (OUTN)
SPK_P: J501.1, U501.9 (OUTP)
VSYS: C501.1, C502.1, U501.7 (VDD), U501.8 (VDD); also elsewhere on the board

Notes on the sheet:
A · Alto-falante: MAX98357A no mesmo I2S do codec, mono (L+R)/2; SD_MODE pelo pino 12.
